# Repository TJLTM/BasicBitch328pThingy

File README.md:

# BasicBitch328pThingy

This is a basic Bitch. 
Made with the Atmel 328p DIP model 
Has 3 Buffered inputs
Has 3 VDC outputs 
Pulled out the remaining pins for 
ability to add other things. I'd 
rate the Outputs ~ 1A a piece 
but probably shouldn't do that 
traces won't handle it. Design 
it for triggering 12 volt 
relays.

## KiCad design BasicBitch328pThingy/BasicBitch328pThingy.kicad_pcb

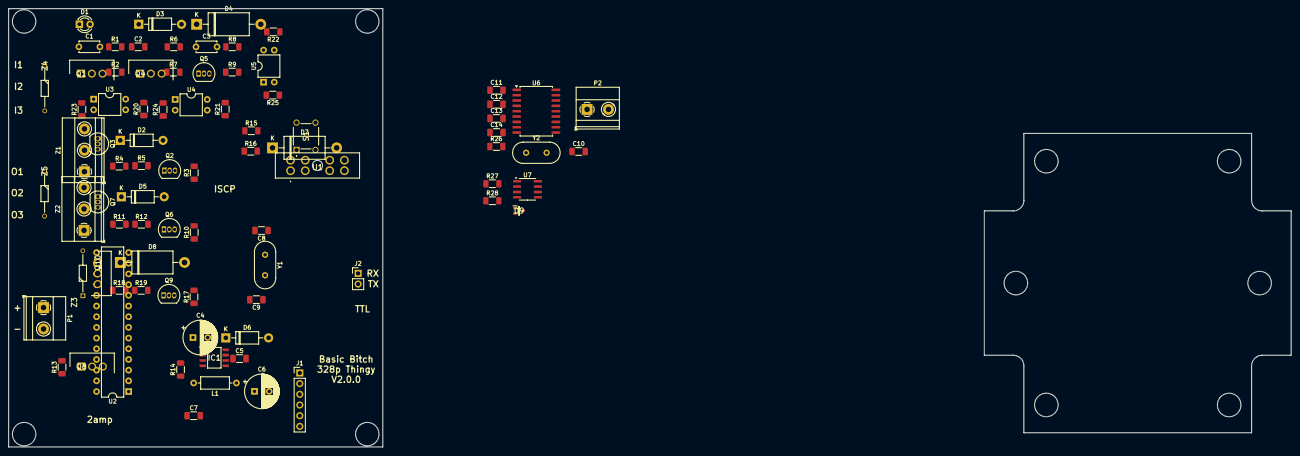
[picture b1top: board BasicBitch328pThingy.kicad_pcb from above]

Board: 2 copper layers, 304.7 x 104.0 mm, 82 parts (0 on the bottom side), 59 nets, no tracks yet.

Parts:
C1, C3: 0.1uF; C_Disc_D4.7mm_W2.5mm_P5.00mm
C2, C13, C14: 100nf; C_1206_3216Metric_Pad1.33x1.80mm_HandSolder
C4: 68uF; CP_Radial_D8.0mm_P3.50mm
C5, C7: 22pF; C_1206_3216Metric_Pad1.33x1.80mm_HandSolder
C6: 120uF; CP_Radial_D8.0mm_P3.50mm
C8, C9, C10: 220nF; C_1206_3216Metric_Pad1.33x1.80mm_HandSolder
C11, C12: 22pf; C_1206_3216Metric_Pad1.33x1.80mm_HandSolder
D1: LED; LED_D3.0mm
D2: 1N5817; D_DO-41_SOD81_P10.16mm_Horizontal
D3, D5, D6: 1N4007; D_DO-41_SOD81_P10.16mm_Horizontal
D4, D7, D8: STPS3150RL; D_DO-201_P15.24mm_Horizontal
D9: PESD5V0L2UU,115; SOT65P210X110-3N
IC1: LM2597MX-5.0_NOPB; SOIC127P600X175-8N
J1: TTL_Programmer; PinHeader_1x06_P2.54mm_Vertical
J2: Conn_01x02; PinHeader_1x02_P2.54mm_Vertical
L1: 150uH; L_Axial_L6.6mm_D2.7mm_P10.16mm_Horizontal_Vishay_IM-2
P1, P2: Screw_Terminal_01x02; TerminalBlock_Phoenix_MKDS-1,5-2-5.08_1x02_P5.08mm_Horizont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
Q1, Q4, Q8, Q10: IRF9Z34NPBF; TO254P469X1042X1967-3P
Q2, Q3, Q5, Q6, Q7, Q9: 2N7000; TO-92_Inline
R1, R4, R11, R22, R25, R26: 10k; R_1206_3216Metric_Pad1.30x1.75mm_HandSolder
R2, R3: 330; R_1206_3216Metric_Pad1.30x1.75mm_HandSolder
R5, R12, R16: 470; R_1206_3216Metric_Pad1.30x1.75mm_HandSolder
R6, R7, R8, R13, R14, R15, R17, R18, R19: 5k; R_1206_3216Metric_Pad1.30x1.75mm_HandSolder
R9, R20, R23: 1M; R_1206_3216Metric_Pad1.30x1.75mm_HandSolder
R10, R21, R24: 100k; R_1206_3216Metric_Pad1.30x1.75mm_HandSolder
R27: 17k; R_1206_3216Metric_Pad1.30x1.75mm_HandSolder
R28: 120; R_1206_3216Metric_Pad1.30x1.75mm_HandSolder
S1: TS02-66-160-BK-260-LCR-D; TS0266160BK260LCRD
U1: 178.6165.0001; 17861650001
U2: ATmega328-P; DIP-28_W7.62mm
U3, U4, U5: LTV-817; DIP-4_W7.62mm
U6: MCP2515-xSO; SOIC-18W_7.5x11.6mm_P1.27mm
U7: MCP2551-I-SN; SOIC-8_3.9x4.9mm_P1.27mm
Y1: Crystal; Crystal_HC49-U_Vertical
Y2: 16MHz; Crystal_HC49-U_Vertical
Z1, Z2: Screw_Terminal_01x03; TerminalBlock_Phoenix_MKDS-1,5-3-5.08_1x03_P5.08mm_Horizont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
Z3, Z4, Z5: BZX79C10; DIOAD1068W53L380D172

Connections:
+5V: C6.1, C13.1, C14.1, IC1.3 (BIAS_SUPPLY), IC1.4 (FEEDBACK), J1.3, L1.2, R2.1, R7.1, R8.1, R14.1, R15.1, R18.1, R19.1, R26.2, U2.7 (VCC), U2.20 (AVCC), U2.21 (AREF), U6.18 (VDD), U7.3 (VDD)
+VDC: C4.1, IC1.7 (+VIN), Q4.3, Q8.3, Q10.3, R4.1, R10.1, R21.1, R24.1, U1.1, U1.2, U1.7, U1.8, Z3.1, Z4.1, Z5.1
/CANBUS-MCP2515/RXtoCANTC: U6.2 (RXCAN), U7.4 (RXD)
/CANBUS-MCP2515/TXtoCANTC: U6.1 (TXCAN), U7.1 (TXD)
/CANBUS-MCP2551/CANH: D9.1 (CATHODE_1), J2.1, P2.2, U7.7 (CANH)
/CANBUS-MCP2551/CANL: D9.2 (CATHODE_2), P2.1, R28.2, U7.6 (CANL)
/Input1/Input: C9.1, D5.1 (K), R12.1, Z2.2
/Input2/Input: C10.1, D6.1 (K), R16.1, Z2.3
/Input/Input: C8.1, D3.1 (K), R5.1, Z2.1
/Output1/Output: D7.1 (K), Q8.2, Z1.2
/Output2/Output: D8.1 (K), Q10.2, Z1.3
/Output/Output: D4.1 (K), Q4.2, Z1.1
D8: U2.14 (PB0), U6.12 (~INT)
D10: U2.16 (PB2), U6.16 (~CS)
GND: C1.2, C3.2, C4.2, C5.2, C6.2, C7.2, C8.2, C9.2, C10.2, C11.2, C12.2, C13.2, C14.2, D2.2 (A), D4.2 (A), D7.2 (A), D8.2 (A), D9.3 (COMMON_ANODE), IC1.6 (GROUND), J1.1, P1.2, Q2.1 (S), Q3.1 (S), Q5.1 (S), Q6.1 (S), Q7.1 (S), Q9.1 (S), R1.2, R3.2, R6.2, R9.2, R13.2, R17.2, R20.2, R23.2, R27.2, S1.3 (COM_1), U2.8 (GND), U2.22 (GND), U3.3, U4.3, U5.3, U6.9 (VSS), U7.2 (VSS)
Input1: R8.2, U2.5 (PD3), U3.4
Input2: R15.2, U2.6 (PD4), U4.4
Input3: R19.2, U2.4 (PD2), U5.4
LED: D1.2 (A), U2.13 (PD7)
MISO: U2.18 (PB4), U6.15 (SO)
MOSI: U2.17 (PB3), U6.14 (SI)
unnamed: D1.1 (K), R3.1
unnamed: D2.1 (K), IC1.8 (OUTPUT), L1.1
unnamed: D3.2 (A), Q2.2 (G), R5.2, R6.1
unnamed: D5.2 (A), Q5.2 (G), R12.2, R13.1
unnamed: D6.2 (A), Q6.2 (G), R16.2, R17.1
unnamed: C1.1, IC1.2 (DELAY)
unnamed: IC1.1 (ERROR_FLAG), R4.2
unnamed: C3.1, IC1.5 (~SHUTDOWN/SOFT-START)
unnamed: C2.1, J1.6
unnamed: J2.2, R28.1
unnamed: P1.1, Q1.2
unnamed: Q1.1, R1.1
unnamed: Q1.3, U1.3, U1.4, U1.5, U1.6
unnamed: Q2.3 (D), U3.2
unnamed: Q3.3 (D), R11.2
unnamed: Q4.1, R10.2, R11.1, Z3.2
unnamed: Q5.3 (D), U4.2
unnamed: Q6.3 (D), U5.2
unnamed: Q7.3 (D), R22.2
unnamed: Q8.1, R21.2, R22.1, Z4.2
unnamed: Q9.3 (D), R25.2
unnamed: Q10.1, R24.2, R25.1, Z5.2
unnamed: R7.2, U3.1
unnamed: R14.2, U4.1
unnamed: R18.2, U5.1
unnamed: C5.1, U2.9 (XTAL1/PB6), Y1.1
unnamed: C7.1, U2.10 (XTAL2/PB7), Y1.2
unnamed: C12.1, U6.8 (OSC1), Y2.1
unnamed: C11.1, U6.7 (OSC2), Y2.2
unnamed: R26.1, U6.17 (~RESET)
unnamed: R27.1, U7.8 (Rs)
Output1: Q3.2 (G), R9.1, U2.11 (PD5)
Output2: Q7.2 (G), R20.1, U2.12 (PD6)
Output3: Q9.2 (G), R23.1, U2.15 (PB1)
RXttl: J1.4, U2.2 (PD0)
Reset: R2.2, S1.1 (NO_1), U2.1 (~RESET/PC6)
SCK: U2.19 (PB5), U6.13 (SCK)
TXttl: J1.5, U2.3 (PD1)

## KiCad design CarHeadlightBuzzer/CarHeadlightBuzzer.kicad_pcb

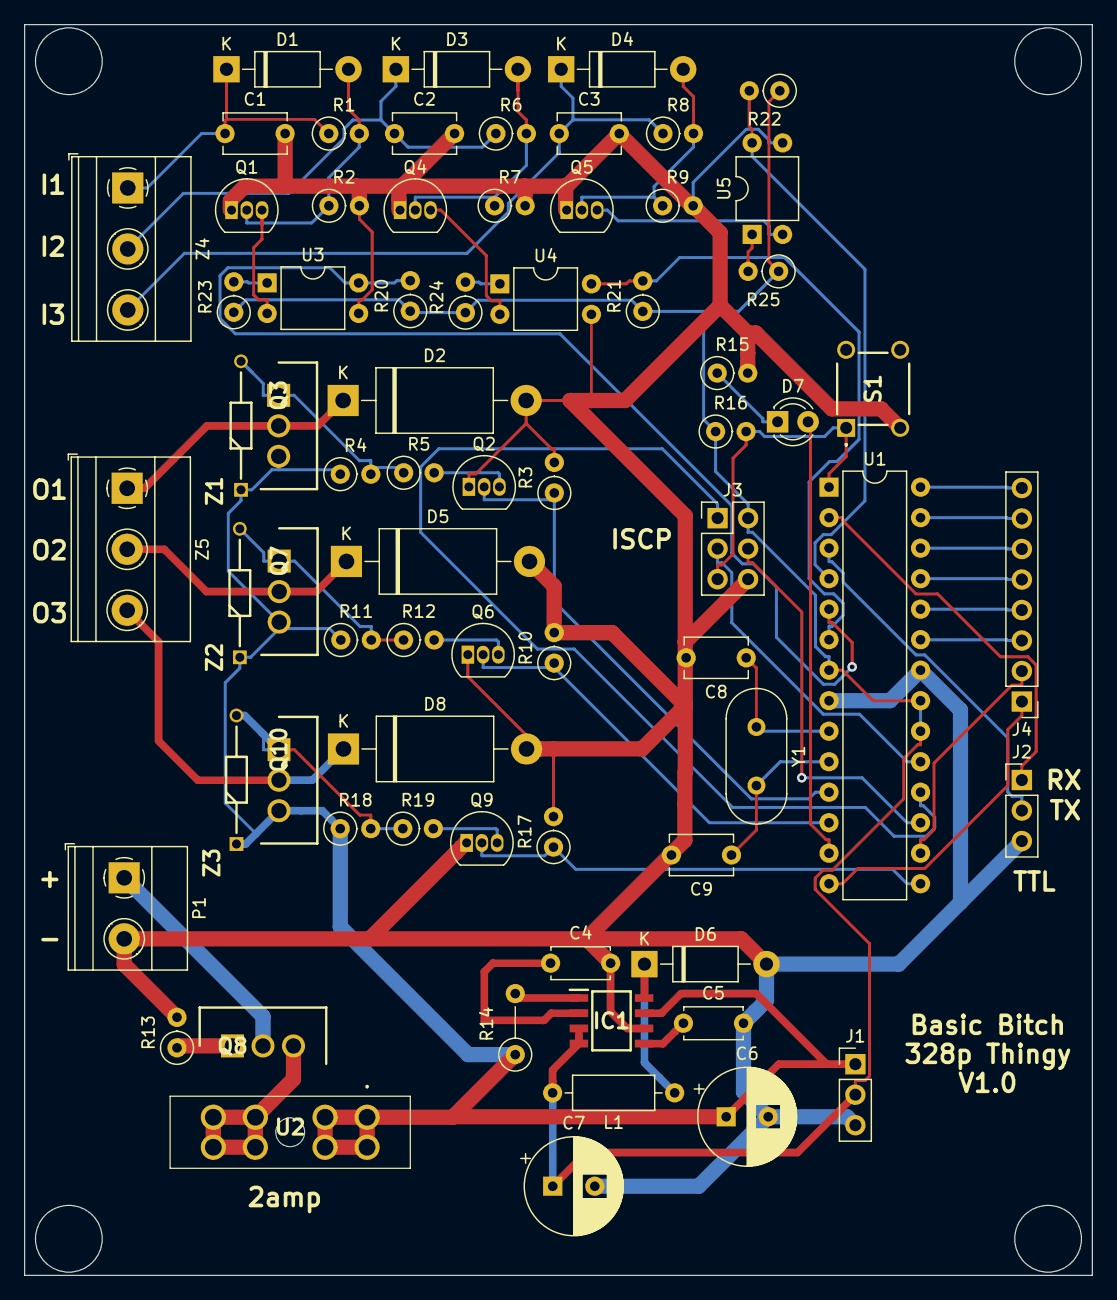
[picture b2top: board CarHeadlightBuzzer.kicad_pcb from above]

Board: 2 copper layers, 88.9 x 104.1 mm, 71 parts (0 on the bottom side), 55 nets.

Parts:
C1, C2, C3, C8, C9: 220nF; C_Disc_D5.1mm_W3.2mm_P5.00mm
C4, C5: 0.1uF; C_Disc_D4.7mm_W2.5mm_P5.00mm
C6: 68uF; CP_Radial_D8.0mm_P3.50mm
C7: 120uF; CP_Radial_D8.0mm_P3.50mm
D1, D3, D4: 1N4007; D_DO-41_SOD81_P10.16mm_Horizontal
D2, D5, D8: STPS3150RL; D_DO-201_P15.24mm_Horizontal
D6: 1N5817; D_DO-41_SOD81_P10.16mm_Horizontal
D7: LED; LED_D3.0mm
IC1: LM2597MX-5.0_NOPB; SOIC127P600X175-8N
J1, J2: Conn_01x03; PinHeader_1x03_P2.54mm_Vertical
J3: Conn_02x03_Odd_Even; PinHeader_2x03_P2.54mm_Vertical
J4: Conn_01x08; PinHeader_1x08_P2.54mm_Vertical
L1: 150uH; L_Axial_L6.6mm_D2.7mm_P10.16mm_Horizontal_Vishay_IM-2
P1: Screw_Terminal_01x02; TerminalBlock_Phoenix_MKDS-1,5-2-5.08_1x02_P5.08mm_Horizont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
Q1, Q2, Q4, Q5, Q6, Q9: 2N7000; TO-92_Inline
Q3, Q7, Q8, Q10: IRF9Z34NPBF; TO254P469X1042X1967-3P
R1, R6, R8: 470; R_Axial_DIN0207_L6.3mm_D2.5mm_P2.54mm_Vertical
R2, R7, R9, R20, R21, R22, R23, R24, R25: 5k; R_Axial_DIN0207_L6.3mm_D2.5mm_P2.54mm_Vertical
R3, R10, R17: 1M; R_Axial_DIN0207_L6.3mm_D2.5mm_P2.54mm_Vertical
R4, R11, R18: 100k; R_Axial_DIN0207_L6.3mm_D2.5mm_P2.54mm_Vertical
R5, R12, R13, R19: 10k; R_Axial_DIN0207_L6.3mm_D2.5mm_P2.54mm_Vertical
R14: 10k; R_Axial_DIN0207_L6.3mm_D2.5mm_P5.08mm_Vertical
R15, R16: 330; R_Axial_DIN0207_L6.3mm_D2.5mm_P2.54mm_Vertical
S1: TS02-66-160-BK-260-LCR-D; TS0266160BK260LCRD
U1: ATmega328-P; DIP-28_W7.62mm
U2: 178.6165.0001; 17861650001
U3, U4, U5: LTV-817; DIP-4_W7.62mm
Y1: Crystal; Crystal_HC49-U_Vertical
Z1, Z2, Z3: BZX79C10; DIOAD1068W53L380D172
Z4, Z5: Screw_Terminal_01x03; TerminalBlock_Phoenix_MKDS-1,5-3-5.08_1x03_P5.08mm_Horizont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

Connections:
+5V: C7.1, IC1.3 (BIAS_SUPPLY), IC1.4 (FEEDBACK), J1.2, J3.2, L1.2, R16.1, R20.1, R21.1, R22.1, R23.1, R24.1, R25.1, U1.7 (VCC), U1.20 (AVCC), U1.21 (AREF)
+VDC: C6.1, IC1.7 (+VIN), J1.1, Q3.3, Q7.3, Q10.3, R4.1, R11.1, R14.1, R18.1, U2.1, U2.2, U2.7, U2.8, Z1.1, Z2.1, Z3.1
/Input1/Input: C2.1, D3.1 (K), R6.1, Z4.2
/Input2/Input: C3.1, D4.1 (K), R8.1, Z4.3
/Input/Input: C1.1, D1.1 (K), R1.1, Z4.1
/Output1/Output: D5.1 (K), Q7.2, Z5.2
/Output2/Output: D8.1 (K), Q10.2, Z5.3
/Output/Output: D2.1 (K), Q3.2, Z5.1
A0: J4.3, U1.23 (PC0)
A1: J4.4, U1.24 (PC1)
A2: J4.5, U1.25 (PC2)
A3: J4.6, U1.26 (PC3)
A4: J4.7, U1.27 (PC4)
A5: J4.8, U1.28 (PC5)
D8: J4.1, U1.14 (PB0)
D10: J4.2, U1.16 (PB2)
GND: C1.2, C2.2, C3.2, C4.2, C5.2, C6.2, C7.2, C8.2, C9.2, D2.2 (A), D5.2 (A), D6.2 (A), D8.2 (A), IC1.6 (GROUND), J1.3, J2.3, J3.6, P1.2, Q1.1 (S), Q2.1 (S), Q4.1 (S), Q5.1 (S), Q6.1 (S), Q9.1 (S), R2.2, R3.2, R7.2, R9.2, R10.2, R13.2, R15.2, R17.2, S1.3 (COM_1), U1.8 (GND), U1.22 (GND), U3.3, U4.3, U5.3
Input1: R20.2, U1.5 (PD3), U3.4
Input2: R21.2, U1.6 (PD4), U4.4
Input3: R22.2, U1.4 (PD2), U5.4
LED: D7.2 (A), U1.13 (PD7)
MISO: J3.1, U1.18 (PB4)
MOSI: J3.4, U1.17 (PB3)
unnamed: D1.2 (A), Q1.2 (G), R1.2, R2.1
unnamed: D3.2 (A), Q4.2 (G), R6.2, R7.1
unnamed: D4.2 (A), Q5.2 (G), R8.2, R9.1
unnamed: D6.1 (K), IC1.8 (OUTPUT), L1.1
unnamed: D7.1 (K), R15.1
unnamed: C4.1, IC1.2 (DELAY)
unnamed: IC1.1 (ERROR_FLAG), R14.2
unnamed: C5.1, IC1.5 (~SHUTDOWN/SOFT-START)
unnamed: P1.1, Q8.2
unnamed: Q1.3 (D), U3.2
unnamed: Q2.3 (D), R5.2
unnamed: Q3.1, R4.2, R5.1, Z1.2
unnamed: Q4.3 (D), U4.2
unnamed: Q5.3 (D), U5.2
unnamed: Q6.3 (D), R12.2
unnamed: Q7.1, R11.2, R12.1, Z2.2
unnamed: Q8.1, R13.1
unnamed: Q8.3, U2.3, U2.4, U2.5, U2.6
unnamed: Q9.3 (D), R19.2
unnamed: Q10.1, R18.2, R19.1, Z3.2
unnamed: R23.2, U3.1
unnamed: R24.2, U4.1
unnamed: R25.2, U5.1
unnamed: C8.1, U1.9 (XTAL1/PB6), Y1.1
unnamed: C9.1, U1.10 (XTAL2/PB7), Y1.2
Output1: Q2.2 (G), R3.1, U1.11 (PD5)
Output2: Q6.2 (G), R10.1, U1.12 (PD6)
Output3: Q9.2 (G), R17.1, U1.15 (PB1)
RXttl: J2.1, U1.2 (PD0)
Reset: J3.5, R16.2, S1.1 (NO_1), U1.1 (~RESET/PC6)
SCK: J3.3, U1.19 (PB5)
TXttl: J2.2, U1.3 (PD1)

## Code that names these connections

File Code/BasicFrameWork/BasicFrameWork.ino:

#define Input1 3
#define Input2 4
#define Input3 2
#define Output1 5
#define Output2 6
#define Output3 9
#define LED 7


void setup() {
  pinMode(Input1, INPUT);
  pinMode(Input2, INPUT);
  pinMode(Input3, INPUT);
  pinMode(Output1, OUTPUT);
  pinMode(Output2, OUTPUT);
  pinMode(Output3, OUTPUT);
  pinMode(LED, OUTPUT);

}

void loop() {


}

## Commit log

2023-05-01 initial design
2023-05-01 adding the code in.
2023-05-03 some routing
2023-05-03 post routed and switched out the crystal needs to be inspected
2023-05-03 last bits of stuff
2023-05-03 removing this
2023-05-03 rename
2023-05-03 rename of folder
2023-05-03 removing README.md
2023-05-03 adding fab files pcbway zip
2023-05-15 V1.0.1
    * Fixed a trace issue
    * updated Fab Files
    * added bom/ibom.html
    * added some code
    ** BasicFrameWork.ino
    ** Test.ino
2023-05-20 updating to have the correct pin outs.
2023-07-14 some tweaks.
2024-05-27 Create LICENSE
2024-05-28 revamping this to have a CANBus Interface and swaping things to a SMD to save Space.
2025-03-02 Revert "Create LICENSE"
    This reverts commit 58dc4c7f4ffe62159fcebb9f62027702740cd1db.
2025-03-02 Revert "updating to have the correct pin outs."
    This reverts commit a5202e797f862cd26f941edca5d2a58ef8195523.
